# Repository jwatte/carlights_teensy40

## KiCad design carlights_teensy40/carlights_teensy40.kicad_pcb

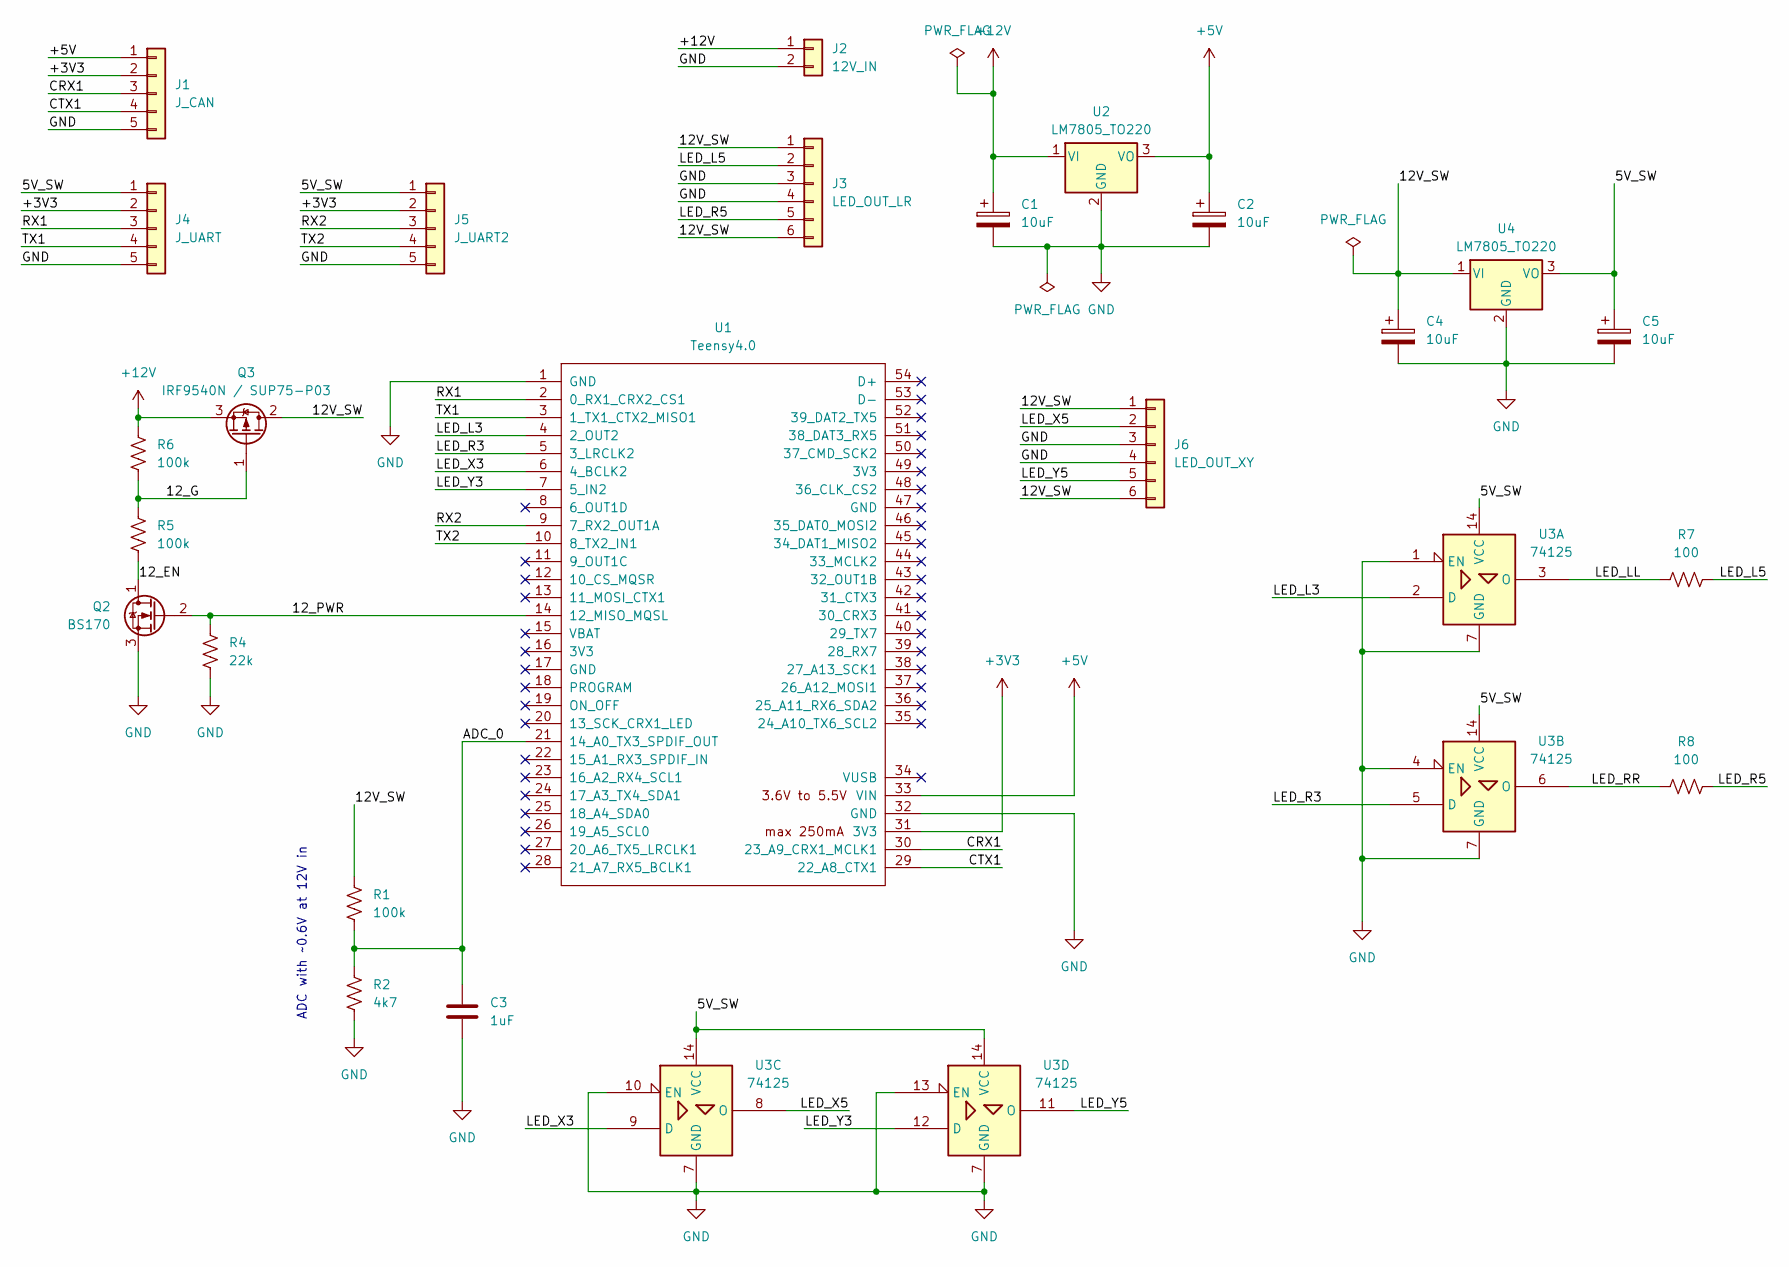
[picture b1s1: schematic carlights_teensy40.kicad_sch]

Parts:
C1, C2, C4, C5: 10uF; CP_Radial_D6.3mm_P2.50mm
C3: 1uF; C_Radial_D5.0mm_H5.0mm_P2.00mm
J1: J_CAN; PinHeader_1x05_P2.54mm_Vertical
J2: 12V_IN; TerminalBlock_bornier-2_P5.08mm
J3: LED_OUT_LR; PinHeader_1x06_P2.54mm_Vertical
J4: J_UART; PinHeader_1x05_P2.54mm_Vertical
J5: J_UART2; PinHeader_1x05_P2.54mm_Vertical
J6: LED_OUT_XY; PinHeader_1x06_P2.54mm_Vertical
Q2: BS170; TO-92_Inline
Q3: IRF9540N / SUP75-P03; TO-220-3_Vertical
R1, R5, R6: 100k; R_Axial_DIN0207_L6.3mm_D2.5mm_P10.16mm_Horizontal
R2: 4k7; R_Axial_DIN0207_L6.3mm_D2.5mm_P10.16mm_Horizontal
R4: 22k; R_Axial_DIN0207_L6.3mm_D2.5mm_P10.16mm_Horizontal
R7, R8: 100; R_Axial_DIN0207_L6.3mm_D2.5mm_P10.16mm_Horizontal
U1: Teensy4.0; Teensy40
U2, U4: LM7805_TO220; TO-220-3_Vertical
U3: 74125; CERDIP-14_W7.62mm_SideBrazed_LongPads_Socket

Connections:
+3V3: J1.2, J4.2, J5.2, U1.31 (3V3)
+5V: C2.1, J1.1, U1.33 (VIN), U2.3 (VO)
+12V: C1.1, J2.1, Q3.3 (S), R6.1, U2.1 (VI)
/5V_SW: C5.1, J4.1, J5.1, U3.14 (VCC), U4.3 (VO)
/12V_SW: C4.1, J3.1, J3.6, J6.1, J6.6, Q3.2 (D), R1.1, U4.1 (VI)
/12_EN: Q2.1 (D), R5.2
/12_G: Q3.1 (G), R5.1, R6.2
/12_PWR: Q2.2 (G), R4.1, U1.14 (12_MISO_MQSL)
/ADC_0: C3.1, R1.2, R2.1, U1.21 (14_A0_TX3_SPDIF_OUT)
/CRX1: J1.3, U1.30 (23_A9_CRX1_MCLK1)
/CTX1: J1.4, U1.29 (22_A8_CTX1)
/LED_L3: U1.4 (2_OUT2), U3.2 (D)
/LED_L5: J3.2, R7.2
/LED_LL: R7.1, U3.3 (O)
/LED_R3: U1.5 (3_LRCLK2), U3.5 (D)
/LED_R5: J3.5, R8.2
/LED_RR: R8.1, U3.6 (O)
/LED_X3: U1.6 (4_BCLK2), U3.9 (D)
/LED_X5: J6.2, U3.8 (O)
/LED_Y3: U1.7 (5_IN2), U3.12 (D)
/LED_Y5: J6.5, U3.11 (O)
/RX1: J4.3, U1.2 (0_RX1_CRX2_CS1)
/RX2: J5.3, U1.9 (7_RX2_OUT1A)
/TX1: J4.4, U1.3 (1_TX1_CTX2_MISO1)
/TX2: J5.4, U1.10 (8_TX2_IN1)
GND: C1.2, C2.2, C3.2, C4.2, C5.2, J1.5, J2.2, J3.3, J3.4, J4.5, J5.5, J6.3, J6.4, Q2.3 (S), R2.2, R4.2, U1.1 (GND), U1.32 (GND), U2.2 (GND), U3.1 (EN), U3.4 (EN), U3.7 (GND), U3.10 (EN), U3.13 (EN), U4.2 (GND)

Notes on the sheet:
ADC with ~0.6V at 12V in

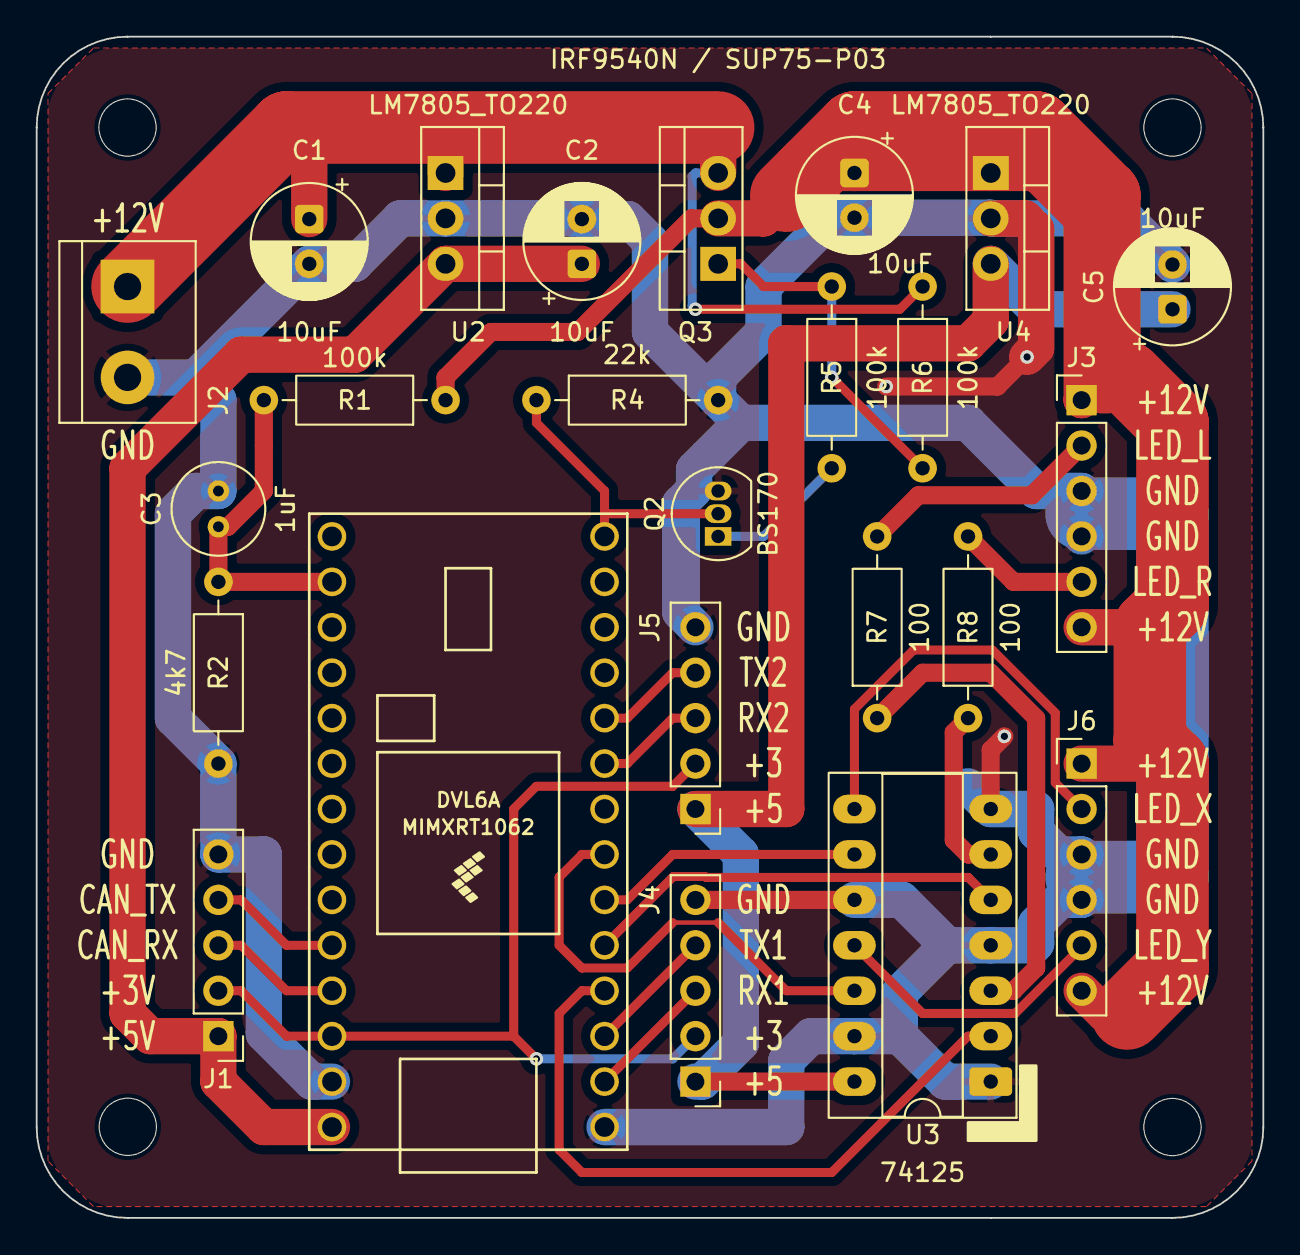
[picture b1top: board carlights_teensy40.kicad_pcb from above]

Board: 2 copper layers, 68.6 x 66.0 mm, 24 parts (0 on the bottom side), 26 nets.

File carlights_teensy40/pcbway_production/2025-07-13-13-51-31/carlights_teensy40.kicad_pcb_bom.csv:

Designator,Quantity,Value,Footprint,Package,MPN,DNP,Mount_Type,Description
"C1, C2, C4, C5",4,10uF,CP_Radial_D6.3mm_P2.50mm,,,,tht,Polarized capacitor
C3,1,1uF,C_Radial_D5.0mm_H5.0mm_P2.00mm,,,,tht,Unpolarized capacitor
J1,1,J_CAN,PinHeader_1x05_P2.54mm_Vertical,,,,tht,"Generic connector, single row, 01x05, script generated (kicad-library-utils/schlib/autogen/connector/)"
J2,1,12V_IN,TerminalBlock_bornier-2_P5.08mm,,,,tht,"Generic connector, single row, 01x02, script generated (kicad-library-utils/schlib/autogen/connector/)"
J3,1,LED_OUT_LR,PinHeader_1x06_P2.54mm_Vertical,,,,tht,"Generic connector, single row, 01x06, script generated (kicad-library-utils/schlib/autogen/connector/)"
J4,1,J_UART,PinHeader_1x05_P2.54mm_Vertical,,,,tht,"Generic connector, single row, 01x05, script generated (kicad-library-utils/schlib/autogen/connector/)"
J5,1,J_UART2,PinHeader_1x05_P2.54mm_Vertical,,,,tht,"Generic connector, single row, 01x05, script generated (kicad-library-utils/schlib/autogen/connector/)"
J6,1,LED_OUT_XY,PinHeader_1x06_P2.54mm_Vertical,,,,tht,"Generic connector, single row, 01x06, script generated (kicad-library-utils/schlib/autogen/connector/)"
Q2,1,BS170,TO-92_Inline,,,,tht,"0.5A Id, 60V Vds, N-Channel MOSFET, TO-92"
Q3,1,IRF9540N / SUP75-P03,TO-220-3_Vertical,,,,tht,"-23A Id, -100V Vds, 117mOhm Rds, P-Channel HEXFET Power MOSFET, TO-220"
"R1, R5, R6",3,100k,R_Axial_DIN0207_L6.3mm_D2.5mm_P10.16mm_Horizontal,,,,tht,"Resistor, US symbol"
R2,1,4k7,R_Axial_DIN0207_L6.3mm_D2.5mm_P10.16mm_Horizontal,,,,tht,"Resistor, US symbol"
R4,1,22k,R_Axial_DIN0207_L6.3mm_D2.5mm_P10.16mm_Horizontal,,,,tht,"Resistor, US symbol"
"R7, R8",2,100,R_Axial_DIN0207_L6.3mm_D2.5mm_P10.16mm_Horizontal,,,,tht,"Resistor, US symbol"
U1,1,Teensy4.0,Teensy40,,,,tht,
"U2, U4",2,78SR05,TO-220-3_Vertical,,,,tht,"Murata Positive 1A 35V Switching Regulator, Fixed Output 5V, TO-220"
U3,1,74125,CERDIP-14_W7.62mm_SideBrazed_LongPads_Socket,,,,tht,

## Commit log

2025-08-31 'software'
2025-08-31 diagnostics features
